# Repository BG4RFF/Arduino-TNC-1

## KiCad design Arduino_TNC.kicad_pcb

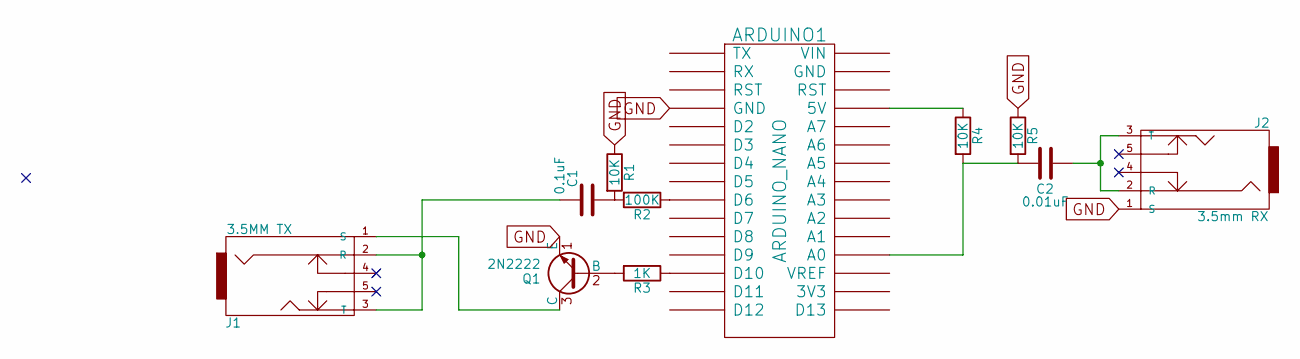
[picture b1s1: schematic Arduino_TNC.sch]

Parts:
ARDUINO1: ARDUINO_NANO; Arduino_Nano
C1: 0.1uF; C_0805_HandSoldering
C2: 0.01uF; C_0805_HandSoldering
J1: 3.5MM TX; Tayda_3.5mm_stereo_TRS_jack_A-853
J2: 3.5mm RX; Tayda_3.5mm_stereo_TRS_jack_A-853
Q1: 2N2222; TO-92_Molded_Wide
R1, R4, R5: 10K; R_0805_HandSoldering
R2: 100K; R_0805_HandSoldering
R3: 1K; R_0805_HandSoldering

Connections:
GND: ARDUINO1.4 (GND), J2.1 (S), Q1.1 (E), R1.1, R5.1
unnamed 9: ARDUINO1.9 (D6), R2.1; also elsewhere on the board
unnamed 13: ARDUINO1.13 (D10), R3.1; also elsewhere on the board
unnamed 19: ARDUINO1.19 (A0), C2.1, R4.2, R5.2; also elsewhere on the board
unnamed 27: ARDUINO1.27 (5V), R4.1; also elsewhere on the board
unnamed: C1.1, R1.2, R2.2
unnamed: C1.2, J1.2 (R), J1.3 (T)
unnamed: C2.2, J2.2 (R), J2.3 (T)
unnamed: J1.1 (S), Q1.3 (C)
unnamed: Q1.2 (B), R3.2

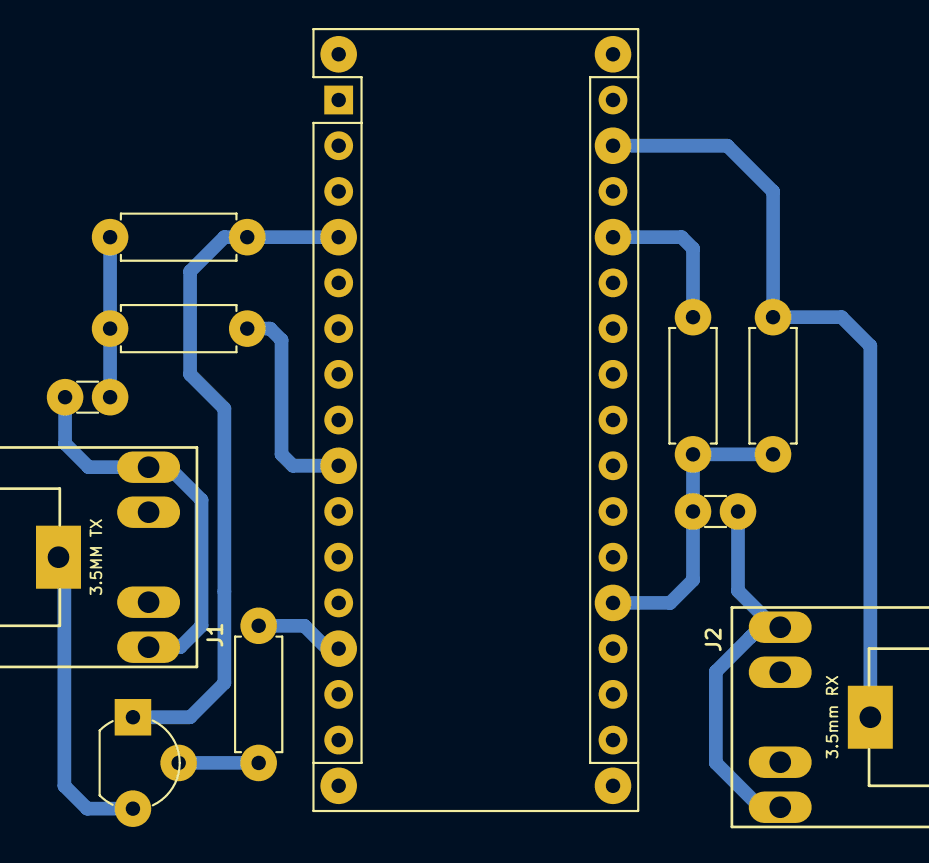
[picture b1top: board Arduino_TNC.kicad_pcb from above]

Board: 2 copper layers, 11 parts (0 on the bottom side), 10 nets.

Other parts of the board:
ARDUINO NANO: ARDUINO_NANO; Arduino_Nano_WithMountingHoles

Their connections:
unnamed 9: ARDUINO NANO.9; also elsewhere on the board
unnamed 13: ARDUINO NANO.13; also elsewhere on the board
unnamed 19: ARDUINO NANO.19; also elsewhere on the board
unnamed 27: ARDUINO NANO.27; also elsewhere on the board

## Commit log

2017-10-27 Add proper printable PCB board
